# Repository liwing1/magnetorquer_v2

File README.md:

# magnetorquer_v2
HW &amp; SW for the new LODESTAR magnetorquer project

## Preparando firmware para validação de hardware:
  - Sistemas de Clocks:
    - [X] DCO;
    - [X] Oscilador Externo.
  - Pinos de entrada e saída:
    - [X] Acionar LEDs;
    - [X] Alimentar Sensores.
  - Acionamento das bobinas:
    - [X] Garação dos sinais PWM;
    - [ ] Magnetômetro;
  - Comunicação Serial:
    - [ ] Acelerômetro & Giroscópio;
    - [X] Conector PC104

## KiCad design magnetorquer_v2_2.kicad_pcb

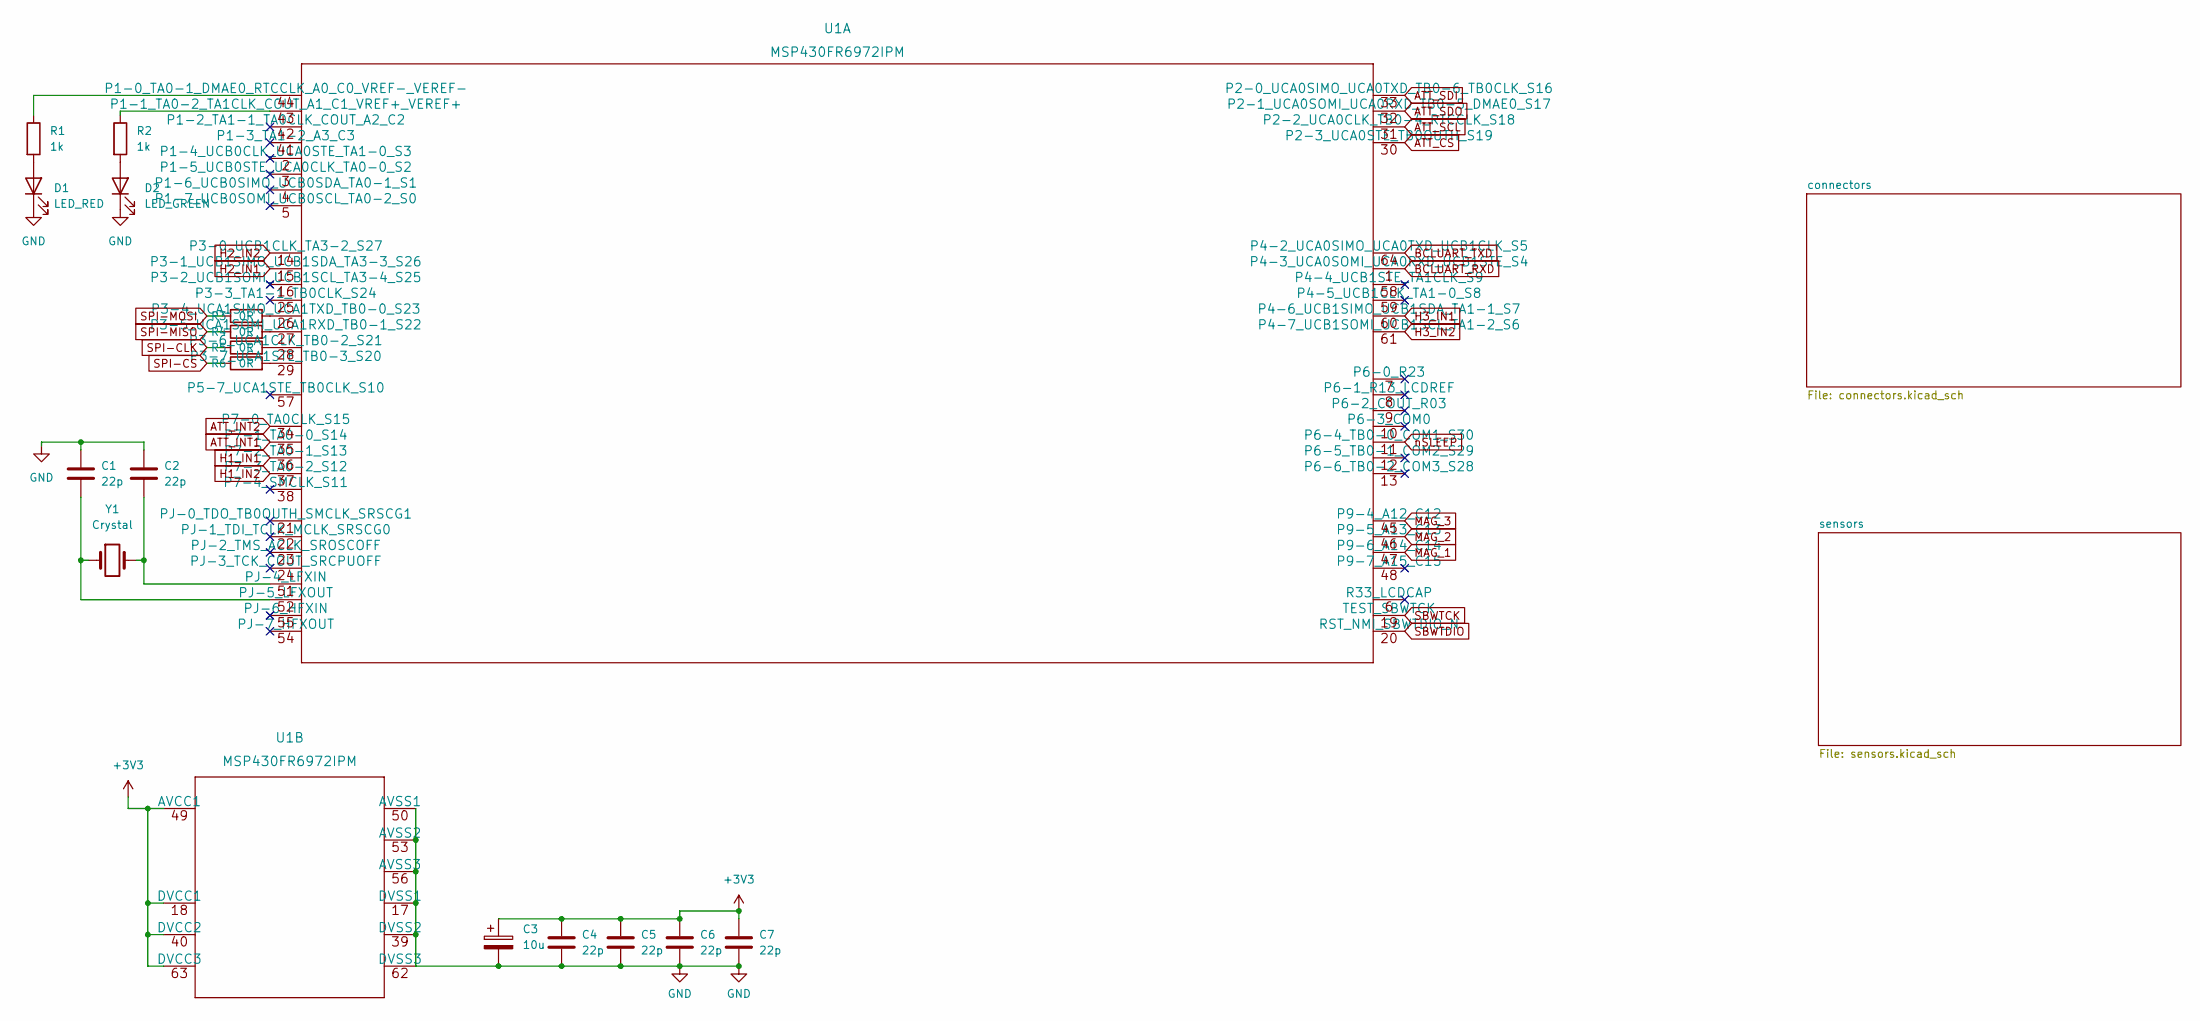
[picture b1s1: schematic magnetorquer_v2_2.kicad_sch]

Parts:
C1, C2, C4, C5, C6, C7: 22p; C_0805_2012Metric
C3: 10u; CP_EIA-3216-18_Kemet-A
D1: LED_RED; LED_0603_1608Metric
D2: LED_GREEN; LED_0603_1608Metric
R1, R2: 1k; R_0805_2012Metric
R3, R4, R5, R6: 0R; R_0805_2012Metric
U1: MSP430FR6972IPM
Y1: Crystal; Crystal_HC49-4H_Vertical

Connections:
+3V3: C3.1, C4.1, C5.1, C6.1, C7.1, U1.18 (DVCC1), U1.40 (DVCC2), U1.49 (AVCC1), U1.63 (DVCC3); also elsewhere on the board
ATT_CS: U1.30 (P2-3_UCA0STE_TB0OUTH_S19); also elsewhere on the board
ATT_INT1: U1.35 (P7-1_TA0-0_S14); also elsewhere on the board
ATT_INT2: U1.34 (P7-0_TA0CLK_S15); also elsewhere on the board
ATT_SCL: U1.31 (P2-2_UCA0CLK_TB0-4_RTCCLK_S18); also elsewhere on the board
ATT_SDI: U1.33 (P2-0_UCA0SIMO_UCA0TXD_TB0-6_TB0CLK_S16); also elsewhere on the board
ATT_SDO: U1.32 (P2-1_UCA0SOMI_UCA0RXD_TB0-5_DMAE0_S17); also elsewhere on the board
BCLUART_RXD: U1.1 (P4-3_UCA0SOMI_UCA0RXD_UCB1STE_S4); also elsewhere on the board
BCLUART_TXD: U1.64 (P4-2_UCA0SIMO_UCA0TXD_UCB1CLK_S5); also elsewhere on the board
GND: C1.1, C2.1, C3.2, C4.2, C5.2, C6.2, C7.2, D1.1 (K), D2.1 (K), U1.17 (DVSS1), U1.39 (DVSS2), U1.50 (AVSS1), U1.53 (AVSS2), U1.56 (AVSS3), U1.62 (DVSS3); also elsewhere on the board
H1_IN1: U1.36 (P7-2_TA0-1_S13); also elsewhere on the board
H1_IN2: U1.37 (P7-3_TA0-2_S12); also elsewhere on the board
H2_IN1: U1.15 (P3-1_UCB1SIMO_UCB1SDA_TA3-3_S26); also elsewhere on the board
H2_IN2: U1.14 (P3-0_UCB1CLK_TA3-2_S27); also elsewhere on the board
H3_IN1: U1.60 (P4-6_UCB1SIMO_UCB1SDA_TA1-1_S7); also elsewhere on the board
H3_IN2: U1.61 (P4-7_UCB1SOMI_UCB1SCL_TA1-2_S6); also elsewhere on the board
MAG_1: U1.47 (P9-6_A14_C14); also elsewhere on the board
MAG_2: U1.46 (P9-5_A13_C13); also elsewhere on the board
MAG_3: U1.45 (P9-4_A12_C12); also elsewhere on the board
unnamed: C1.2, U1.52 (PJ-5_LFXOUT), Y1.1
unnamed: C2.2, U1.51 (PJ-4_LFXIN), Y1.2
unnamed: D1.2 (A), R1.2
unnamed: D2.2 (A), R2.2
unnamed: R1.1, U1.44 (P1-0_TA0-1_DMAE0_RTCCLK_A0_C0_VREF-_VER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)
unnamed: R2.1, U1.43 (P1-1_TA0-2_TA1CLK_COUT_A1_C1_VREF+_VERE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)
unnamed: R3.2, U1.26 (P3-4_UCA1SIMO_UCA1TXD_TB0-0_S23)
unnamed: R4.2, U1.27 (P3-5_UCA1SOMI_UCA1RXD_TB0-1_S22)
unnamed: R5.2, U1.28 (P3-6_UCA1CLK_TB0-2_S21)
unnamed: R6.2, U1.29 (P3-7_UCA1STE_TB0-3_S20)
SBWTCK: U1.19 (TEST_SBWTCK); also elsewhere on the board
SBWTDIO: U1.20 (RST_NMI_SBWTDIO_N); also elsewhere on the board
SPI-CLK: R5.1; also elsewhere on the board
SPI-CS: R6.1; also elsewhere on the board
SPI-MISO: R4.1; also elsewhere on the board
SPI-MOSI: R3.1; also elsewhere on the board
nSLEEP: U1.11 (P6-4_TB0-0_COM1_S30); also elsewhere on the board

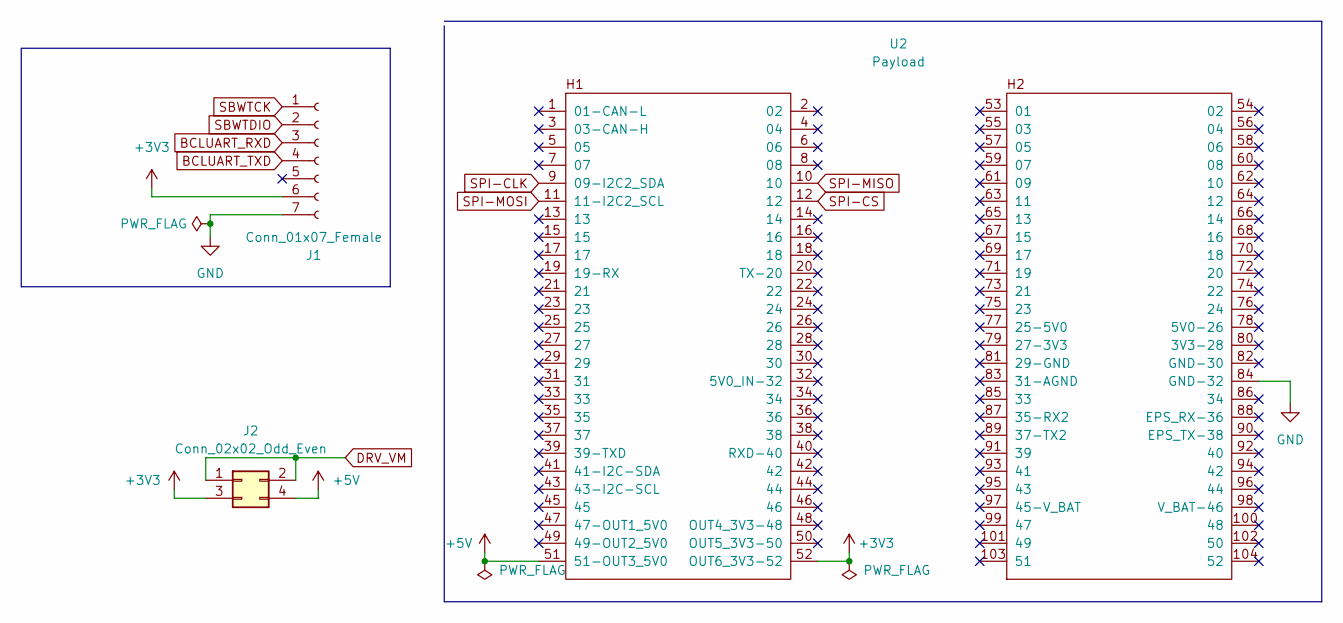
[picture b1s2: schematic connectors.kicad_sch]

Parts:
J1: Conn_01x07_Female; PinHeader_1x07_P2.54mm_Vertical
J2: Conn_02x02_Odd_Even; PinHeader_2x02_P2.54mm_Vertical
U2: Payload; PC104-Standard

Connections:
+3V3: J1.6, J2.3, U2.52 (OUT6_3V3-52); also elsewhere on the board
+5V: J2.4, U2.51 (51-OUT3_5V0)
BCLUART_RXD: J1.3; also elsewhere on the board
BCLUART_TXD: J1.4; also elsewhere on the board
GND: J1.7, U2.84 (GND-32); also elsewhere on the board
SBWTCK: J1.1; also elsewhere on the board
SBWTDIO: J1.2; also elsewhere on the board
SPI-CLK: U2.9 (09-I2C2_SDA); also elsewhere on the board
SPI-CS: U2.12; also elsewhere on the board
SPI-MISO: U2.10; also elsewhere on the board
SPI-MOSI: U2.11 (11-I2C2_SCL); also elsewhere on the board

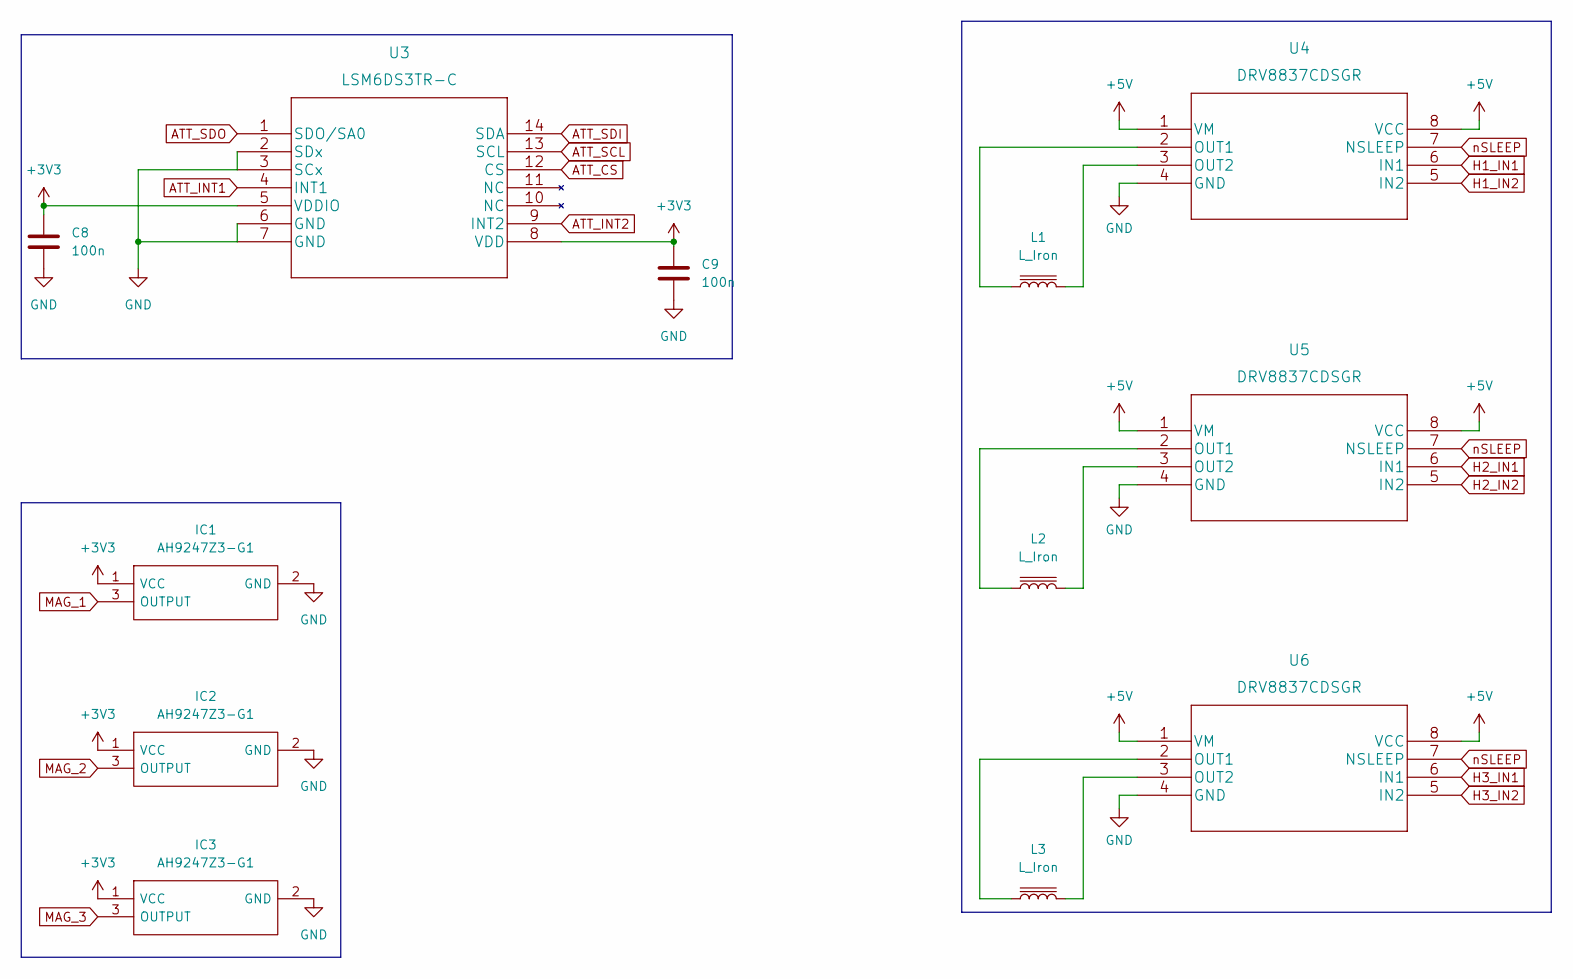
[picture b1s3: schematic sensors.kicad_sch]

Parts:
C8, C9: 100n; C_0805_2012Metric
IC1, IC2, IC3: AH9247Z3-G1; TO-92Flat; Mouser Part Number 621-AH9247Z3-G1
L1, L2, L3: L_Iron; magnetorquer
U3: LSM6DS3TR-C
U4, U5, U6: DRV8837CDSGR

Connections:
+3V3: C8.1, C9.1, IC1.1 (VCC), IC2.1 (VCC), IC3.1 (VCC), U3.5 (VDDIO), U3.8 (VDD); also elsewhere on the board
ATT_CS: U3.12 (CS); also elsewhere on the board
ATT_INT1: U3.4 (INT1); also elsewhere on the board
ATT_INT2: U3.9 (INT2); also elsewhere on the board
ATT_SCL: U3.13 (SCL); also elsewhere on the board
ATT_SDI: U3.14 (SDA); also elsewhere on the board
ATT_SDO: U3.1 (SDO/SA0); also elsewhere on the board
GND: C8.2, C9.2, IC1.2 (GND), IC2.2 (GND), IC3.2 (GND), U3.2 (SDx), U3.3 (SCx), U3.6 (GND), U3.7 (GND), U4.4 (GND), U5.4 (GND), U6.4 (GND); also elsewhere on the board
H1_IN1: U4.6 (IN1); also elsewhere on the board
H1_IN2: U4.5 (IN2); also elsewhere on the board
H2_IN1: U5.6 (IN1); also elsewhere on the board
H2_IN2: U5.5 (IN2); also elsewhere on the board
H3_IN1: U6.6 (IN1); also elsewhere on the board
H3_IN2: U6.5 (IN2); also elsewhere on the board
MAG_1: IC1.3 (OUTPUT); also elsewhere on the board
MAG_2: IC2.3 (OUTPUT); also elsewhere on the board
MAG_3: IC3.3 (OUTPUT); also elsewhere on the board
unnamed: L1.1, U4.2 (OUT1)
unnamed: L1.2, U4.3 (OUT2)
unnamed: L2.1, U5.2 (OUT1)
unnamed: L2.2, U5.3 (OUT2)
unnamed: L3.1, U6.2 (OUT1)
unnamed: L3.2, U6.3 (OUT2)
nSLEEP: U4.7 (NSLEEP), U5.7 (NSLEEP), U6.7 (NSLEEP); also elsewhere on the board

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
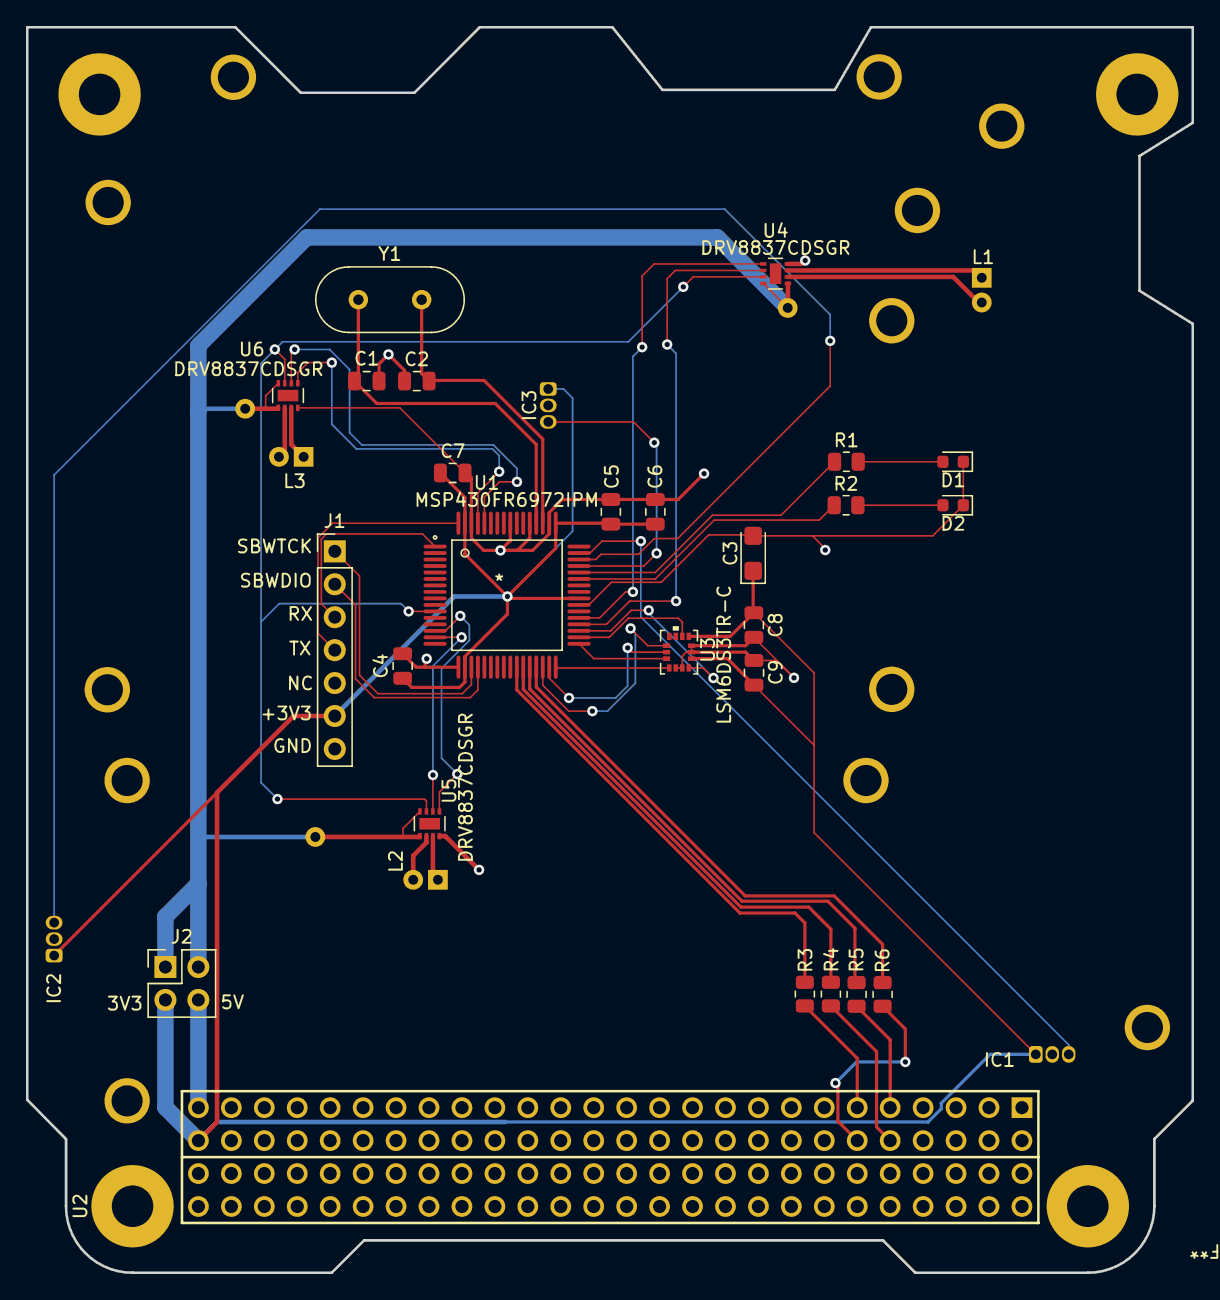
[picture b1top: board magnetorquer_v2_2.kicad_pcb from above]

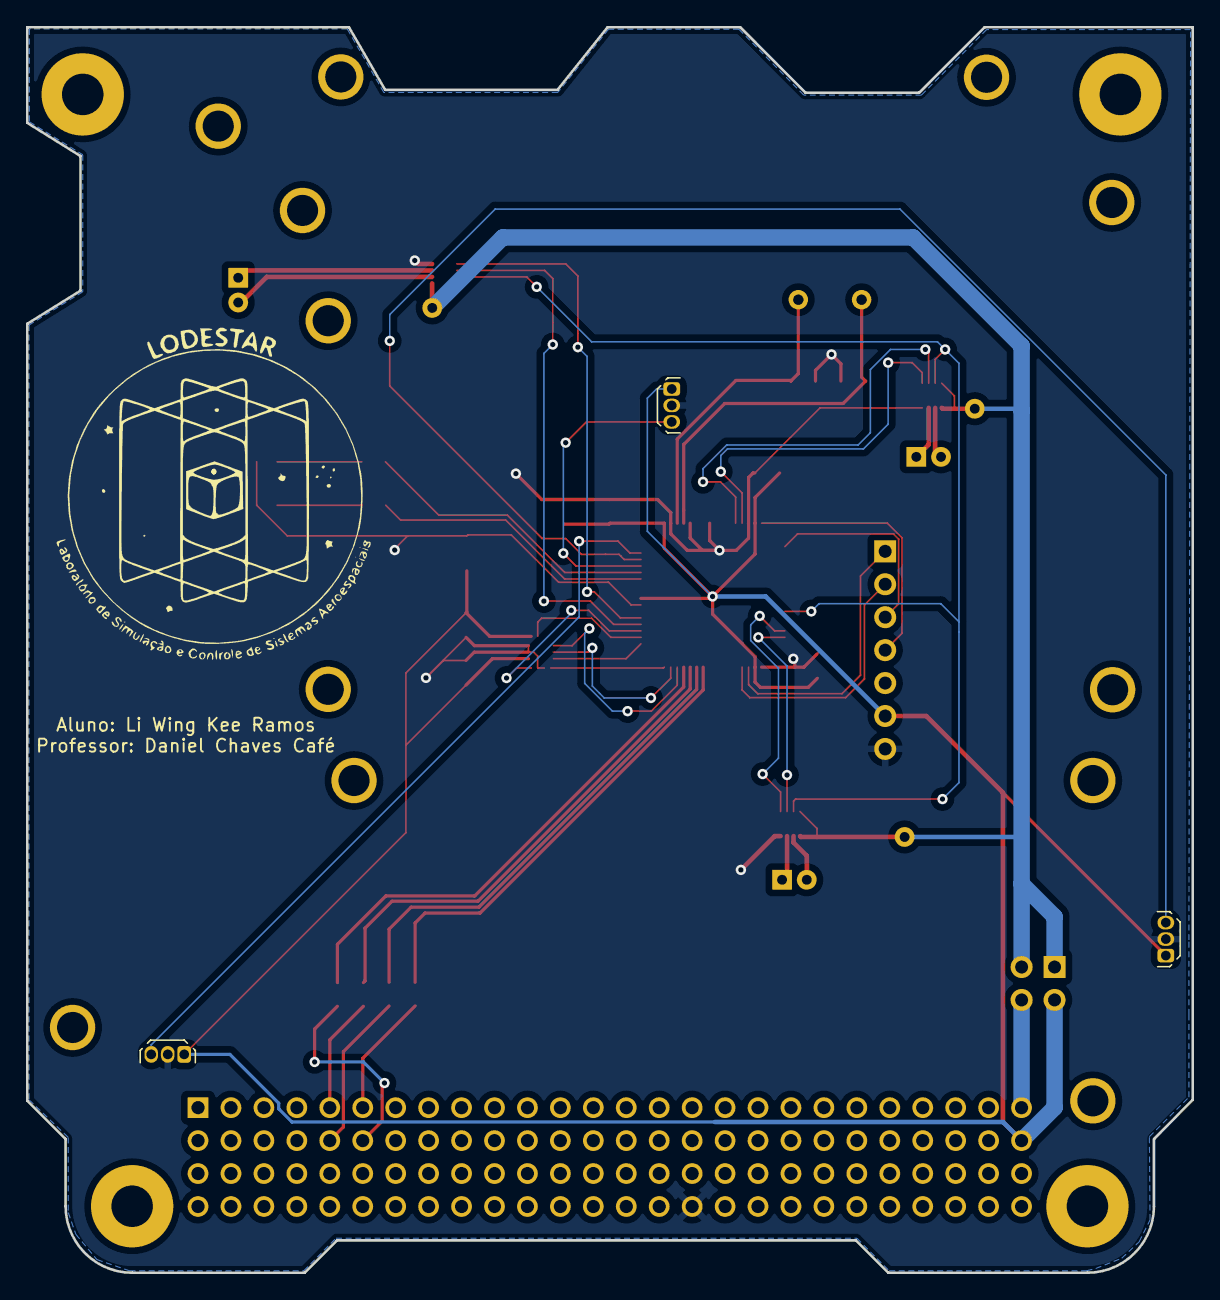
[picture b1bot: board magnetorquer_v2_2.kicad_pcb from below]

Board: 2 copper layers, 89.9 x 96.0 mm, 33 parts (4 on the bottom side), 44 nets.

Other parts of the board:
.: LOGO; logo

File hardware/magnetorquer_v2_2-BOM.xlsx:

Comment | Designator | Footprint | JLCPCB Part #?optional?
DRV8837CDSGR | U5,U6,U4 | DRV8837CDSGR | C191000
0R | R6,R5,R4,R3 | R_0805_2012Metric | C17477
MSP430FR6972IPM | U1 | MSP430FR6972IPM | C472489
10u | C3 | CP_EIA-3216-18_Kemet-A | C110055
22p | C2,C7,C5,C4,C6,C1 | C_0805_2012Metric | C24658
1k | R2,R1 | R_0805_2012Metric | C17513
LED_GREEN | D2 | LED_0603_1608Metric | C87326
LED_RED | D1 | LED_0603_1608Metric | C84263
LSM6DS3TR-C | U3 | LSM6DS3TR-C | C967633
100n | C9,C8 | C_0805_2012Metric | C476766

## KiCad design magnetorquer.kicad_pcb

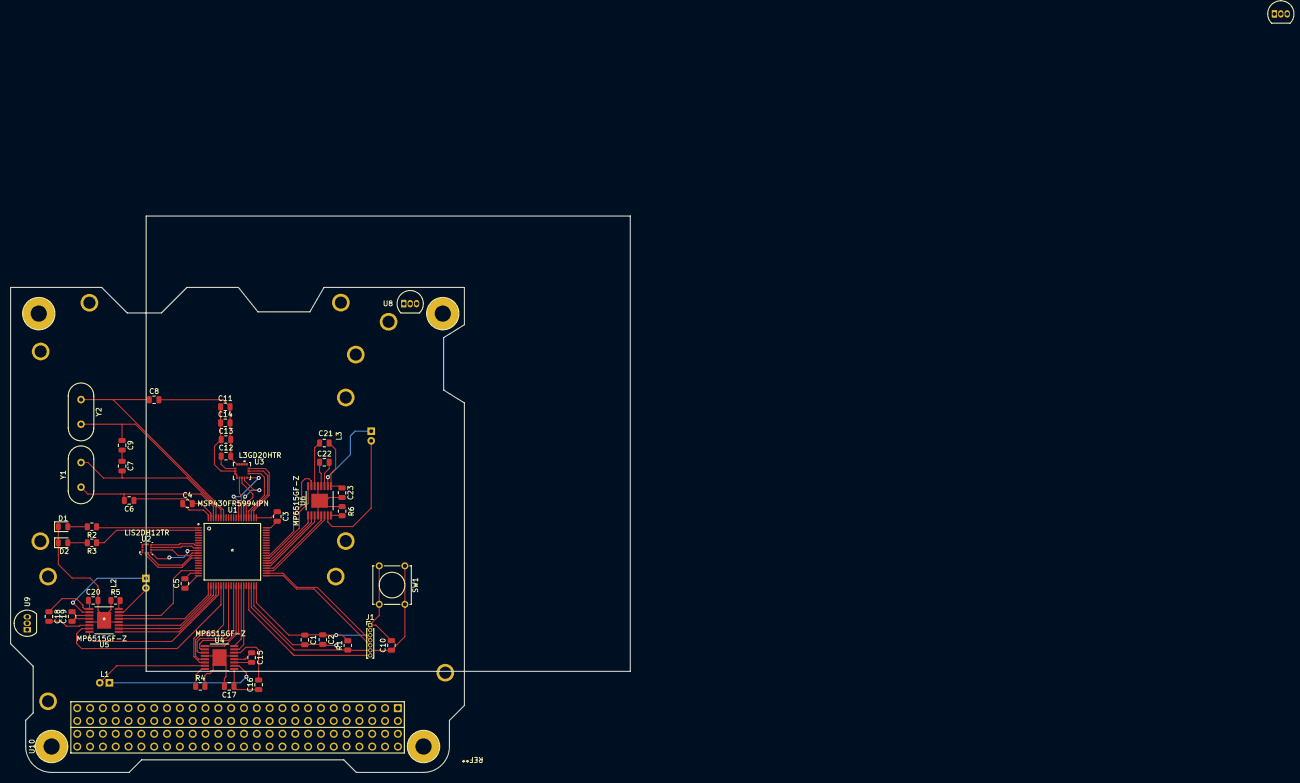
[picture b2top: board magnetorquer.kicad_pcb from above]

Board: 2 copper layers, 122.7 x 110.2 mm, 48 parts (0 on the bottom side), 71 nets.

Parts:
C1: 10u; C_0805_2012Metric
C2, C3, C4, C5, C11, C13, C15, C16, C17, C18, C19, C20, C21, C22, C23: 100n; C_0805_2012Metric
C6, C7: 22p; C_0805_2012Metric
C8, C9: DNP; C_0805_2012Metric
C10: 1n; C_0805_2012Metric
C12, C14: 10n; C_0805_2012Metric
D1: LED_R; LED_0805_2012Metric
D2: LED_G; LED_0805_2012Metric
J1: Conn_01x07_Female; PinHeader_1x07_P1.00mm_Vertical
L1, L2, L3: L_Iron; magnetorquer
R1, R4, R5, R6: 47k; R_0805_2012Metric
R2, R3: 1k; R_0805_2012Metric
SW1: SW_Push; SW_Tactile_Straight_KSL0Axx1LFTR
U1: MSP430FR5994IPN
U2: LIS2DH12TR
U3: L3GD20HTR
U4, U5, U6: MP6515GF-Z
U7, U8, U9: DRV5055A4xLPGxQ1; TO-92_Inline
U10: Payload; PC104-Standard
Y1: Crystal; Crystal_HC49-4H_Vertical
Y2: DNP; Crystal_HC49-4H_Vertical

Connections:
+3V3: C1.1, C2.1, C3.1, C4.1, C5.1, C11.1, C13.1, C14.1, C16.1, C17.1, C18.1, C20.1, C21.1, C23.1, J1.3, R1.2, U1.20 (DVCC2), U1.40 (DVCC3), U1.61 (DVCC1), U1.80 (AVCC1), U2.9 (VDD), U2.10 (VDD_IO), U3.1 (VDD_IO), U3.15 (RES), U3.16 (VDD), U4.9 (VIN), U5.9 (VIN), U6.9 (VIN), U10.79 (27-3V3)
+5V: J1.2, U7.1 (VCC), U8.1 (VCC), U9.1 (VCC), U10.77 (25-5V0)
ACCEL_INT1: U1.12 (P4-7), U2.12 (INT1)
ACCEL_INT2: U1.13 (P7-0_UCB2SIMO_UCB2SDA), U2.11 (INT2)
ACCEL_MISO: U1.9 (P6-1_UCA3RXD_UCA3SOMI), U2.3 (SDO/SA0)
ACCEL_MOSI: U1.8 (P6-0_UCA3TXD_UCA3SIMO), U2.4 (SDA/SDI/SDO)
ACCEL_SCK: U1.10 (P6-2_UCA3CLK), U2.1 (SCL/SPC)
ACCEL_SCS: U1.11 (P6-3_UCA3STE), U2.2 (CS)
BCLUART_RXD: J1.4, U1.42 (P2-1_TB0-0_UCA0RXD_UCA0SOMI)
BCLUART_TXD: J1.5, U1.41 (P2-0_TB0-6_UCA0TXD_UCA0SIMO_TB0CLK_ACLK)
GND: C1.2, C2.2, C3.2, C4.2, C5.2, C6.1, C7.1, C8.2, C9.2, C10.2, C11.2, C12.2, C13.2, C14.2, C17.2, C20.2, C23.2, D1.1 (K), D2.1 (K), J1.1, R4.2, R5.2, R6.2, SW1.2, U1.19 (DVSS2), U1.39 (DVSS3), U1.60 (DVSS1), U1.73 (AVSS3), U1.76 (AVSS2), U1.79 (AVSS1), U2.5 (RES), U2.6 (GND), U2.7 (GND), U2.8 (GND), U3.9 (RES), U3.10 (RES), U3.11 (RES), U3.12 (GND), U3.13 (GND), U4.4 (GND), U4.13 (GND), U4.17 (EP), U5.4 (GND), U5.13 (GND), U5.17 (EP), U6.4 (GND), U6.13 (GND), U6.17 (EP), U7.2 (GND), U8.2 (GND), U9.2 (GND), U10.81 (29-GND), U10.83 (31-AGND)
GYRO_DEN: U1.62 (P2-7), U3.8 (DEN)
GYRO_INT1: U1.64 (P2-4_TA1-0_UCA1CLK_A7_C11), U3.6 (DRDY/INT2)
GYRO_INT2: U1.63 (P2-3_TA0-0_UCA1STE_A6_C10), U3.7 (INT1)
GYRO_MISO: U1.66 (P5-5_UCA2RXD_UCA2SOMI_ACLK), U3.4 (SDO/SA0)
GYRO_MOSI: U1.65 (P5-4_UCA2TXD_UCA2SIMO_TB0OUTH), U3.3 (SDA/SDI/SDO)
GYRO_SCK: U1.67 (P5-6_UCA2CLK_TA4-0_SMCLK), U3.2 (SCL/SPC)
GYRO_SCS: U1.68 (P5-7_UCA2STE_TA4-1_MCLK), U3.5 (CS)
H1_BMODE: U1.34 (P4-3_A11), U4.16 (BMODE)
H1_BREAK: U1.32 (P4-1_A9), U4.2 (BRAKE)
H1_ENBL: U1.27 (P7-4__TA4-0_A16), U4.6 (ENBL)
H1_OUT1: L1.1, U4.7 (OUT1)
H1_OUT2: L1.2, U4.10 (OUT2)
H1_PHASE: U1.31 (P4-0_A8), U4.3 (PHASE)
H1_VISEN: U1.35 (P2-5_TB0-0_UCA1TXD_UCA1SIMO), U4.15 (VISEN)
H1_nFAULT: U1.33 (P4-2_A10), U4.1 (NFAULT)
H1_nSLEEP: U1.29 (P7-6_A18), U4.5 (NSLEEP)
H2_BMODE: U1.25 (P7-2_UCB2CLK), U5.16 (BMODE)
H2_BREAK: U1.23 (PJ-2_TMS_ACLK_SROSCOFF_C8), U5.2 (BRAKE)
H2_ENBL: U1.18 (P1-5_TB0-2_UCA0CLK_A5_C5), U5.6 (ENBL)
H2_OUT1: L2.1, U5.7 (OUT1)
H2_OUT2: L2.2, U5.10 (OUT2)
H2_PHASE: U1.22 (PJ-1_TDI_TCLK_MCLK_SRSCG0_C7), U5.3 (PHASE)
H2_VISEN: U1.26 (P7-3_UCB2STE_TA4-1), U5.15 (VISEN)
H2_nFAULT: U1.24 (PJ-3_TCK_SRCPUOFF_C9), U5.1 (NFAULT)
H2_nSLEEP: U1.21 (PJ-0_TDO_TB0OUTH_SMCLK_SRSCG1_C6), U5.5 (NSLEEP)
H3_BMODE: U1.48 (P3-5_TB0-4_COUT), U6.16 (BMODE)
H3_BREAK: U1.46 (P8-3), U6.2 (BRAKE)
H3_ENBL: U1.43 (P2-2_TB0-2_UCB0CLK), U6.6 (ENBL)
H3_OUT1: L3.1, U6.7 (OUT1)
H3_OUT2: L3.2, U6.10 (OUT2)
H3_PHASE: U1.45 (P8-2), U6.3 (PHASE)
H3_VISEN: U1.49 (P3-6_TB0-5), U6.15 (VISEN)
H3_nFAULT: U1.47 (P3-4_TB0-3_SMCLK), U6.1 (NFAULT)
H3_nSLEEP: U1.44 (P8-1), U6.5 (NSLEEP)
MAG_1: U1.6 (P3-2_A14_C14), U7.3 (OUT)
MAG_2: U1.15 (P8-0), U8.3 (OUT)
MAG_3: U1.36 (P2-6_TB0-1_UCA1RXD_UCA1SOMI), U9.3 (OUT)
unnamed: C6.2, U1.78 (PJ-5_LFXOUT), Y1.1
unnamed: C7.2, U1.77 (PJ-4_LFXIN), Y1.2
unnamed: C8.1, U1.74 (PJ-6_HFXIN), Y2.1
unnamed: C9.1, U1.75 (PJ-7_HFXOUT), Y2.2
unnamed: C12.1, U3.14 (CAP)
unnamed: C15.1, U4.12 (CPB)
unnamed: C15.2, U4.11 (CPA)
unnamed: C16.2, U4.14 (VCP)
unnamed: C18.2, U5.14 (VCP)
unnamed: C19.1, U5.12 (CPB)
unnamed: C19.2, U5.11 (CPA)
unnamed: C21.2, U6.14 (VCP)
unnamed: C22.1, U6.12 (CPB)
unnamed: C22.2, U6.11 (CPA)
unnamed: D1.2 (A), R2.2
unnamed: D2.2 (A), R3.2
unnamed: R2.1, U1.1 (P1-0_TA0-1_DMAE0_RTCCLK_A0_C0_VREF-_VeR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)
unnamed: R3.1, U1.2 (P1-1_TA0-2_TA1CLK_COUT_A1_C1_VREF+_VeRE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)
unnamed: R4.1, U4.8 (ISET)
unnamed: R5.1, U5.8 (ISET)
unnamed: R6.1, U6.8 (ISET)
SBWTCK: J1.7, U1.37 (TEST_SBWTCK)
SBWTDIO: C10.1, J1.6, R1.1, SW1.1, U1.38 (RST_NMI_SBWTDIO_N)

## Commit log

2021-10-20 adicionado varios componentes
2022-01-10 wiring sensors
2022-01-21 createb pcb edges
2022-01-28 update to kicad6
2022-01-30 schematic update hall sensor
2022-01-30 start layout
2022-02-01 adicionado conector pc104
2022-02-21 last commit
2022-02-21 restore
2022-02-21 magnetorquer v2_2
2022-02-21 backup upodate
2022-02-21 added coils
2022-03-14 new uc
2022-04-03 v1 fab
2022-04-03 added sw folder
2022-06-13 add gitignore
2022-06-14 update main with uart and spi
2022-06-14 add _DEBUG_ predefined symbol
2022-06-14 implemented SPI
2022-08-25 add timer init
2023-03-14 refactor code
2023-03-27 update kicad refs
2023-03-27 update adc for testing
2023-04-11 add artigos
2023-05-01 convert from bits to mV
2023-05-02 average of adc measures
2023-05-04 DRV fixed
2023-05-04 rename my_pwm to DRV8837
2023-05-04 implemented global timer
2023-05-06 fix timer flags
2023-05-06 convert from mV to Gauss
2023-06-28 low power implemented

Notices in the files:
parts and their libraries:
Copyright 2021 Accelerated Designs. All rights reserved.
